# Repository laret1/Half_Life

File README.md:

# Starbie 🐾

## What is Starbie?

Starbie is a little digital pet, kind of like a Tamagotchi. You have to take care of it, play with it, feed it and make sure it gets some rest is so interesant that tamagochi.

The idea behind this project was to make my own version of a digital pet, but also let other people build one themselves. It has a small screen, sensors and a custom PCB, so you can interact with your pet just by moving the device around i really dont know if it work so dont belive in me already.

## What I made

For this project, I designed the PCB in KiCad and worked on the firmware using Arduino IDE. I wanted Starbie to be more than just a screen with a character on it, so I added different ways to interact with the pet with buttons and that things.

Here is what I worked on:

- Designed a custom PCB using KiCad.
- Used a Seeed XIAO ESP32-C3 as the main microcontroller so the starbi have a brain.
- Added a 128x64 SSD1306 OLED screen to display the pet and its menus so you can see how adorable is.
- Added an MPU6050 to detect tilting and shaking so you can play better with him.
- Included a DHT11 sensor to read temperature and humidity so it have a lot of tecnologia.
- Made a radial menu controlled by tilting the device.
- Added a system to save the pet's stats, so they don't reset every time you turn it off because thats boring.

The firmware is written in Arduino C++ and the idea is to keep the project simple enough for other people to understand and modify.

 How to use it

Starbie has two buttons and an MPU6050 sensor. Most of the interactions are done through the buttons and by moving the device.

Each stat goes from 0 to 100. They change when you interact with Starbie, but they don't automatically decrease while the device is doing nothing.

I also made the stats save to the ESP32-C3's internal non-volatile storage. This means your pet keeps its stats even after restarting the device.

## Hardware and pinout

The project uses a Seeed XIAO ESP32-C3 and a few external modules connected to the custom PCB this is a lot of tecnical things so it was difficult.

| Component | XIAO pin | GPIO |
| --- | --- | --- |
| OLED SDA | D4 | GPIO6 |
| MPU6050 SDA | D4 | GPIO6 |
| OLED SCL | D5 | GPIO7 |
| MPU6050 SCL | D5 | GPIO7 |
| DHT11 data | D1 | GPIO3 |
| Button 1 | D2 | GPIO4 |
| Button 2 | D3 | GPIO5 |

 Software

The firmware is in `Starbie.ino` at the root of the repository.

To work on the project, you will need:

- Arduino IDE
- ESP32 board support for the Seeed XIAO ESP32-C3
- Adafruit GFX Library
- Adafruit SSD1306
- Adafruit MPU6050
- DHT sensor library
else you cant give starbi life
You can install the libraries through **Sketch → Include Library → Manage Libraries** in Arduino IDE. Some libraries may install additional dependencies, so make sure to install those too or you starbi will be sad.

### Uploading the firmware

1. Open `Starbie.ino` in Arduino IDE.
2. Install the required libraries.
3. Connect the XIAO ESP32-C3 to your computer using USB.
4. Select the correct board and serial port.
5. Upload the code.
6. Check that the screen, buttons and sensors are working.

and the starbi is ready to play with you

## Bill of Materials (BOM)

These are the main components used for Starbie. Some parts may depend on the final PCB version, so check the schematic and footprints before ordering anything or you starbi will be incompleted.

| Qty. | Component | Purpose |
| --- | --- | --- |
| 1 | Seeed XIAO ESP32-C3 | Main microcontroller |
| 1 | SSD1306 OLED 128x64 (I2C) | Displays the pet, menus and stats |
| 1 | MPU6050 module | Detects movement, tilting and shaking |
| 1 | DHT11 sensor/module | Measures temperature and humidity |
| 1 | 10kΩ resistor | Used by the circuit; check the final schematic for its exact purpose |
| 2 | MX-compatible mechanical switches | Physical buttons |
| 2 | Compatible keycaps | Used with the mechanical switches |
| 1 | Custom PCB | The board designed in KiCad |
| As needed | Headers and connectors | Connect the modules and other components |

## Project files

Here are the main files included in the repository:

- `Starbi.kicad_pro` — KiCad project settings.
- `Starbi.kicad_sch` — Circuit schematic.
- `Starbi.kicad_pcb` — PCB layout.
- `Starbie.ino` — Arduino firmware.
- `BOM.csv` — Bill of Materials.

If you build your own Starbie or make changes to the project, feel free to experiment with it!

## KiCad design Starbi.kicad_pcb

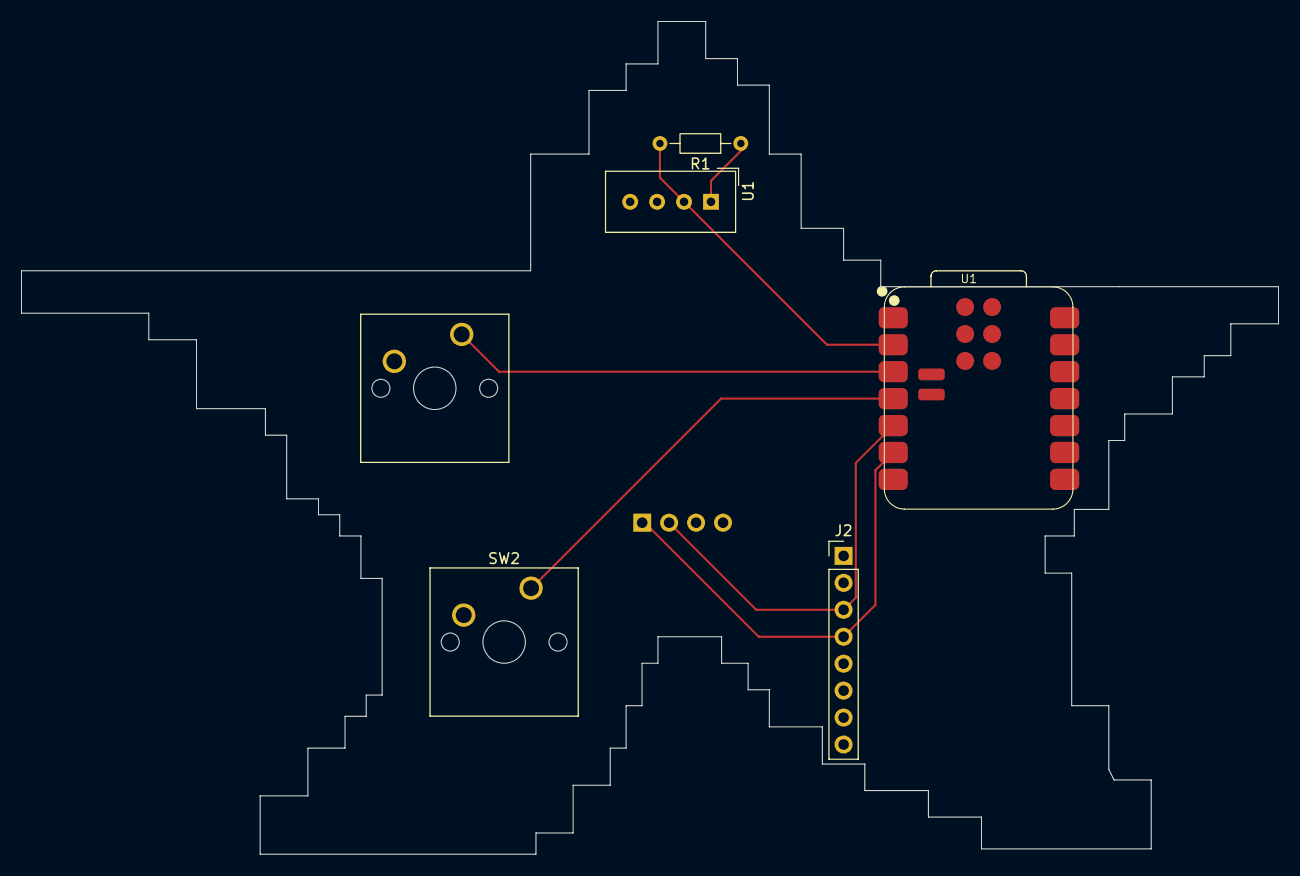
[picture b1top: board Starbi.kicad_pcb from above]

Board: 2 copper layers, 118.5 x 78.5 mm, 7 parts (1 on the bottom side), 7 nets.

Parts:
J1: Conn_01x04_Pin; Display_128x64_096_I2C
J2: Conn_01x08_Pin; PinHeader_1x08_P2.54mm_Vertical
R1: 10K; R_Axial_DIN0204_L3.6mm_D1.6mm_P7.62mm_Horizontal
SW1, SW2: SW_Push; SW_Cherry_MX_1.00u_PCB
U1: DHT11; Aosong_DHT11_5.5x12.0_P2.54mm
U1#2: XIAO-ESP32-C3-SMD

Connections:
+3.3V: J1.2, J2.1, R1.1, U1.1 (VDD), U1#2.12 (3V3_OUT)
/DHT11 DATA: R1.2, U1.2 (DATA), U1#2.2 (D1)
/GP102: SW1.1, U1#2.3 (D2)
/GP103: SW2.1, U1#2.4 (D3)
/SCL: J1.3, J2.3, U1#2.5 (D4)
/SDA: J1.4, J2.4, U1#2.6 (D5)
GND: J1.1, J2.2, SW1.2, SW2.2, U1.4 (GND), U1#2.13 (GND), U1#2.18 (GND)
